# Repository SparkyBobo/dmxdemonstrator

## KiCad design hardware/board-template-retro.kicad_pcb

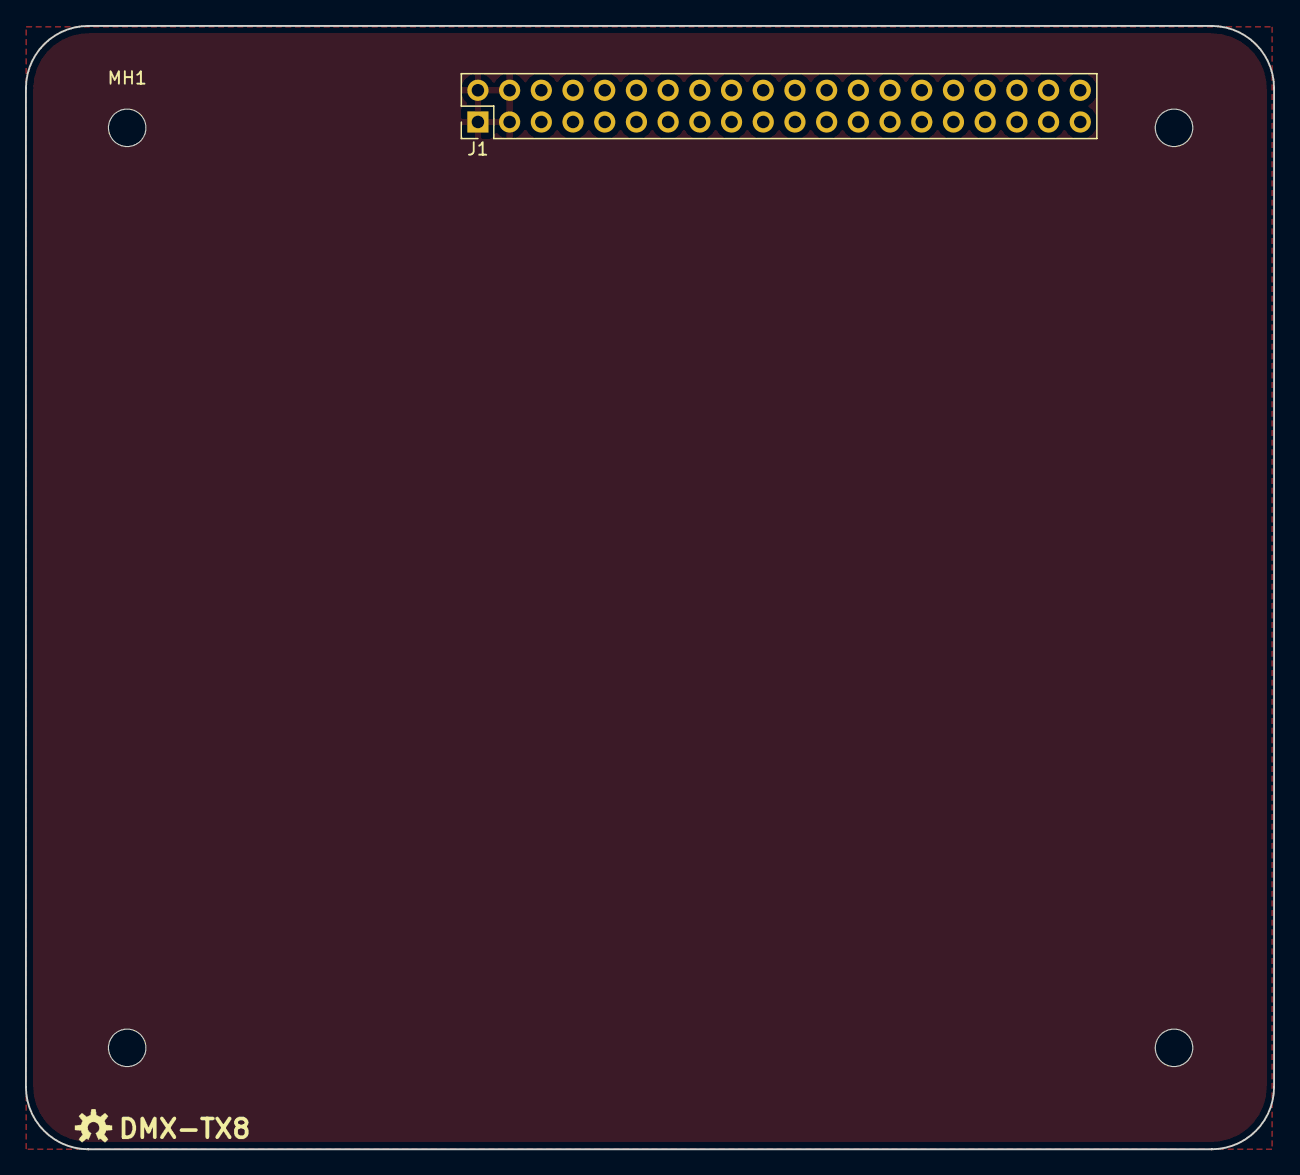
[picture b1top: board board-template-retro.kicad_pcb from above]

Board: 2 copper layers, 100.0 x 90.0 mm, 5 parts (0 on the bottom side), 2 nets, no tracks yet.

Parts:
J1: Expansion; PinHeader_2x20_P2.54mm_Vertical
MH1, MH2, MH3, MH4: MountingHole; MountingHole_3mm

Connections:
+5V: J1.1, J1.2, J1.3, J1.4
GND: J1.37, J1.38, J1.39, J1.40

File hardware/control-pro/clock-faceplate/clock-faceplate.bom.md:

# Bill Of Materials (BOM)

## Schematic

**Filename:** E:\OpenSource\dmxdemonstrator\hardware\control-pro\clock-faceplate\clock-faceplate.sch

**Date Modified:** 4/6/2024 8:51:16 PM

**Kicad Version:** Eeschema (5.1.12)-1

**Component Count:** 17

## Components

Item#|Quantity|Reference|Description|Manufacturer|Part Number|Datasheet|Notes
-----|--------|---------|-----------|------------|-----------|---------|-----
1|1|PCB|Control-Pro Clock Faceplate PCB|OHSPark|DMX-CPCF, Rev 1.3||[Order](https://oshpark.com/shared_projects/S9LARHyr)|
2|4|MH1, MH2, MH3, MH4|Screw, M3 x 8mm||||
<!--BOMROW-->

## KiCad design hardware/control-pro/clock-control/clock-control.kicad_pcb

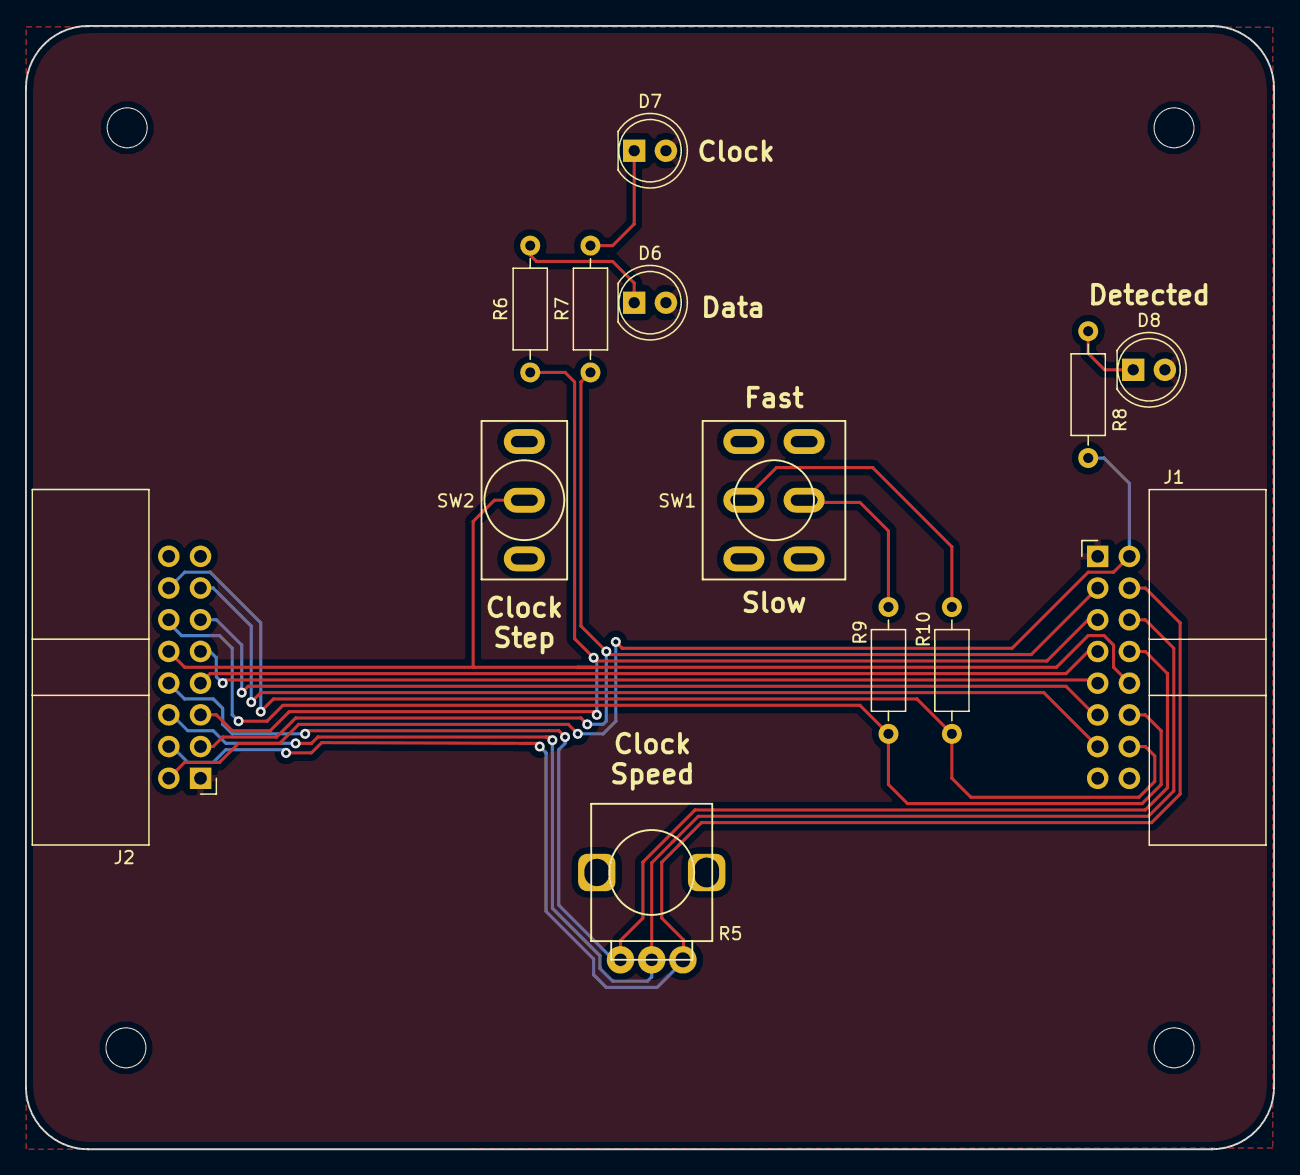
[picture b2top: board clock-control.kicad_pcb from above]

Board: 2 copper layers, 100.0 x 90.0 mm, 17 parts (0 on the bottom side), 20 nets.

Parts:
D6: DATA; LED_D5.0mm
D7: CLOCK; LED_D5.0mm
D8: ACTIVE; LED_D5.0mm
J1: OUTPUT; IDC-Header_2x08_P2.54mm_Horizontal
J2: INPUT; IDC-Header_2x08_P2.54mm_Horizontal
MH1, MH2, MH3, MH4: MountingHole; MountingHole_3.2mm_M3
R5: 10k; BOURNS_PTV09A_1
R6, R7, R8, R9, R10: 330; R_Axial_DIN0207_L6.3mm_D2.5mm_P10.16mm_Horizontal
SW1: CLOCK_SPEED; ESWITCH_100_DPDT_M1
SW2: CLOCK_STEP; ESWITCH_100_SPDT_M1

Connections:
+5V: D6.2, D7.2, D8.2, J1.1, J2.1
/DIM1: J1.7, J2.7
/DIM2: J1.9, J2.9
/DIM3: J1.11, J2.11
/DIM4: J1.13, J2.13
/SPD_HI: J1.4, J2.4, R5.3
/SPD_LO: J1.8, J2.8, R5.1
/SPD_WIPER: J1.6, J2.6, R5.2
/~CLK_FST: J1.14, J2.14, R10.1
/~CLK_SLO: J1.12, J2.12, R9.1
/~CLK_STEP: J1.10, J2.10, SW2.2
/~CLOCK: J1.3, J2.3, R7.1
/~DATA: J1.5, J2.5, R6.1
/~HWD_DT: J1.2, J2.2, R8.1
GND: J1.15, J1.16, J2.15, J2.16, SW1.3, SW1.4, SW2.3
unnamed: D6.1, R6.2
unnamed: D7.1, R7.2
unnamed: D8.1, R8.2
unnamed: R9.2, SW1.2
unnamed: R10.2, SW1.5

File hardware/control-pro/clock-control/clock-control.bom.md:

# Bill Of Materials (BOM)

## Schematic

**Filename:** E:\OpenSource\dmxdemonstrator\hardware\control-pro\clock-control\clock-control.sch

**Date Modified:** 4/8/2024 1:51:22 PM

**Kicad Version:** Eeschema (5.1.12)-1

**Component Count:** 17

## Components

Item#|Quantity|Reference|Description|Manufacturer|Part Number|Datasheet|Notes
-----|--------|---------|-----------|------------|-----------|---------|-----
1|1|PCB|Control-Pro Clock Control PCB|OHSPark|DMX-CPCB, Rev 1.3||[Order](https://oshpark.com/shared_projects/llBuRZd8)|
2|1|D6|Green LED, 5mm||||
3|1|D6|LED Spacer, 17mm|Wurth|705820170|[Data Sheet](https://www.we-online.de/katalog/datasheet/705820xxx_overview.pdf)|
4|1|D7|Red LED, 5mm||||
5|1|D7|LED Spacer, 17mm|Wurth|705820170|[Data Sheet](https://www.we-online.de/katalog/datasheet/705820xxx_overview.pdf)|
6|1|D8|Red LED, 5mm||||
7|1|J1|2x8 shrouded right-angle header|Wurth Elektronik|61201621721|[Data Sheet](https://www.we-online.com/components/products/datasheet/6120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|
8|1|J1|2x8 ribbon cable||||
9|1|J2|2x8 shrouded right-angle header|Wurth Elektronik|61201621721|[Data Sheet](https://www.we-online.com/components/products/datasheet/6120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|
10|4|MH1, MH2, MH3, MH4|Standoff, M3 x 18mm|Keystone|24446||
11|4|MH1, MH2, MH3, MH4|Screw, M3 x 8mm||||
12|1|R5|100k potentiometer, audio|Bourns|PTV09A-4030F-A104|[Data Sheet](https://www.bourns.com/docs/Product-Datasheets/PTV09.pdf)|
13|1|R5|potentiometer knob||||
14|5|R6, R7, R8, R9, R10|330 ohm||||
15|1|SW1|DPDT Toggle, On-Off-On|E-Switch|100DP3T1B1M1QEH|[Data Sheet](https://sten-eswitch-13110800-production.s3.amazonaws.com/sy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|
16|1|SW2|SPDT Toggle, On-On momentary|E-Switch|100SP2T1B1M1QEH|[Data Sheet](https://sten-eswitch-13110800-production.s3.amazonaws.com/sy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|
<!--BOMROW-->

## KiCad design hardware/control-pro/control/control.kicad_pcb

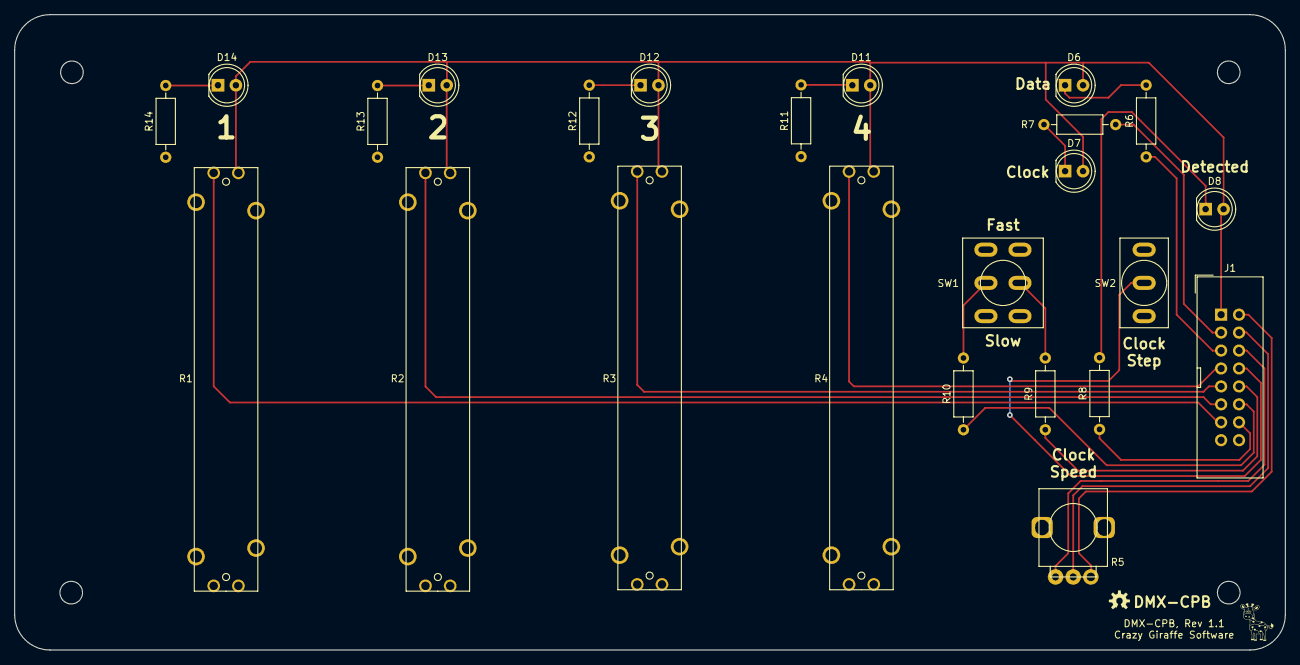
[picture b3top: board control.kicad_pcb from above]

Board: 2 copper layers, 180.0 x 90.0 mm, 28 parts (0 on the bottom side), 24 nets.

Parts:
D6: DATA; LED_D5.0mm
D7: CLOCK; LED_D5.0mm
D8: ACTIVE; LED_D5.0mm
D11: DIM3; LED_D5.0mm
D12: DIM2; LED_D5.0mm
D13: DIM1; LED_D5.0mm
D14: DIM0; LED_D5.0mm
J1: OUTPUT; IDC-Header_2x08_P2.54mm_Vertical
MH1, MH2, MH3, MH4: MountingHole; MountingHole_3.2mm_M3
R1, R2, R3, R4: 10k; BOURNS_PTA4543
R5: 10k; BOURNS_PTV09A_1
R6, R7, R8, R9, R10, R11, R12, R13, R14: 330; R_Axial_DIN0207_L6.3mm_D2.5mm_P10.16mm_Horizontal
SW1: CLOCK_SPEED; ESWITCH_100_DPDT_M1
SW2: CLOCK_STEP; ESWITCH_100_SPDT_M1

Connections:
+5V: D6.2, D7.2, D8.2, D11.2, D12.2, D13.2, D14.2, J1.1, R1.1, R2.1, R3.1, R4.1
GND: J1.15, J1.16, R1.3, R2.3, R3.3, R4.3, R11.1, R12.1, R13.1, R14.1, SW1.3, SW1.4, SW2.3
unnamed: D6.1, R6.2
unnamed: D7.1, R7.2
unnamed: D8.1, R8.2
unnamed: D11.1, R11.2
unnamed: D12.1, R12.2
unnamed: D13.1, R13.2
unnamed: D14.1, R14.2
unnamed: J1.2, R5.3
unnamed: J1.3, R7.1
unnamed: J1.4, R5.2
unnamed: J1.5, R6.1
unnamed: J1.6, R5.1
unnamed: J1.7, R4.2
unnamed: J1.8, SW2.2
unnamed: J1.9, R3.2
unnamed: J1.10, R9.1
unnamed: J1.11, R2.2
unnamed: J1.12, R10.1
unnamed: J1.13, R1.2
unnamed: J1.14, R8.1
unnamed: R9.2, SW1.2
unnamed: R10.2, SW1.5

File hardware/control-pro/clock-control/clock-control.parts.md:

# Parts List

## Schematic

**Filename:** E:\OpenSource\dmxdemonstrator\hardware\control-pro\clock-control\clock-control.sch

**Date Modified:** 4/8/2024 1:51:22 PM

**Kicad Version:** Eeschema (5.1.12)-1

**Component Count:** 17

## Parts


### OHSPark

Reference|Description|Supplier|Part Number|Quantity|Link|Notes
---------|-----------|--------|-----------|--------|----|-----
PCB|Control-Pro Clock Control PCB|OHSPark|DMX-CPCB, Rev 1.3|1|[Order](https://oshpark.com/shared_projects/llBuRZd8)|pack of 3, 2 not used
<!--PARTROW-->

### Sparkfun

Reference|Description|Supplier|Part Number|Quantity|Link|Notes
---------|-----------|--------|-----------|--------|----|-----
D6|Green LED, 5mm|Sparkfun|COM-09592|1|[Order](https://www.sparkfun.com/products/9592)|
D7, D8|Red LED, 5mm|Sparkfun|COM-09590|2|[Order](https://www.sparkfun.com/products/9590)|
R5|potentiometer knob|Sparkfun|COM-11951|1|[Order](https://www.sparkfun.com/products/11951)|goes to 11
R6, R7, R8, R9, R10|330 ohm|Sparkfun|PRT-14490|1|[Order](https://www.sparkfun.com/products/14490)|pack of 20, 15 not used
<!--PARTROW-->

### Adafruit

Reference|Description|Supplier|Part Number|Quantity|Link|Notes
---------|-----------|--------|-----------|--------|----|-----
D6|Green LED, 5mm|Adafruit|298|1|[Order](https://www.adafruit.com/product/298)|pack of 25, 24 not used
D7, D8|Red LED, 5mm|Adafruit|299|1|[Order](https://www.adafruit.com/product/299)|pack of 25, 23 not used
R5|potentiometer knob|Adafruit|5527|1|[Order](https://www.adafruit.com/product/5527)|black, silver, red, blue, gold
R6, R7, R8, R9, R10|330 ohm|Adafruit|2781|1|[Order](https://www.adafruit.com/product/2781)|use 470 ohm instead, pack of 25, 20 not used
<!--PARTROW-->

### Digikey

Reference|Description|Supplier|Part Number|Quantity|Link|Notes
---------|-----------|--------|-----------|--------|----|-----
D6, D7|LED Spacer, 17mm|Digikey|732-11617-ND|2|[Order](https://www.digikey.com/product-detail/en/w%C3%BCrth-elektro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|
J1, J2|2x8 shrouded right-angle header|Digikey| 732-2099-ND|2|[Order](https://www.digikey.com/en/products/detail/w%C3%BCrth-elektr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|
MH1, MH2, MH3, MH4|Standoff, M3 x 18mm|Digikey|36-24446-ND|4|[Order](https://www.digikey.com/product-detail/en/keystone-electroni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|
R5|100k potentiometer, audio|Digikey|PTV09A-4030F-A104-ND|1|[Order](https://www.digikey.com/en/products/detail/bourns-inc/PTV09A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|knob needed
SW1|DPDT Toggle, On-Off-On|Digikey|EG2413-ND|1|[Order](https://www.digikey.com/products/en?keywords=100DP3T1B1M1QEH)|
SW2|SPDT Toggle, On-On momentary|Digikey|EG2373-ND|1|[Order](https://www.digikey.com/product-detail/en/e-switch/100SP2T1B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|
<!--PARTROW-->

### Mouser

Reference|Description|Supplier|Part Number|Quantity|Link|Notes
---------|-----------|--------|-----------|--------|----|-----
D6, D7|LED Spacer, 17mm|Mouser|710-705820170|2|[Order](https://www.mouser.com/ProductDetail/Wurth-Elektronik/705820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|
J1, J2|2x8 shrouded right-angle header|Mouser|710-61201621721|2|[Order](https://www.mouser.com/ProductDetail/Wurth-Elektronik/612016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|
MH1, MH2, MH3, MH4|Standoff, M3 x 18mm|Mouser|534-24436|4|[Order](https://www.mouser.com/ProductDetail/Keystone-Electronics/24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|
R5|100k potentiometer, audio|Mouser|652-PTV09A4030FA104|1|[Order](https://www.mouser.com/ProductDetail/Bourns/PTV09A-4030F-A10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|knob needed
SW1|DPDT Toggle, On-Off-On|Mouser|612-100-H1111|1|[Order](https://www.mouser.com/ProductDetail/E-Switch/100DP3T1B1M1QE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|
SW2|SPDT Toggle, On-On momentary|Mouser|612-100-B1111|1|[Order](https://www.mouser.com/ProductDetail/E-Switch/100SP2T1B1M1QE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|
<!--PARTROW-->

### Newark

Reference|Description|Supplier|Part Number|Quantity|Link|Notes
---------|-----------|--------|-----------|--------|----|-----
J1, J2|2x8 shrouded right-angle header|Newark|19P1272|2|[Order](https://www.newark.com/wurth-elektronik/61201621721/wire-to-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|
<!--PARTROW-->

### Amazon

Reference|Description|Supplier|Part Number|Quantity|Link|Notes
---------|-----------|--------|-----------|--------|----|-----
J1|2x8 ribbon cable|Amazon||1|[Order](https://www.amazon.com/s?k=16-Pin+IDC+Connector+Flat+Ribbon+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|
MH1, MH2, MH3, MH4|Standoff, M3 x 18mm|Amazon||4|[Order](https://www.amazon.com/s?k=m3+18mm+standoff)|
MH1, MH2, MH3, MH4|Screw, M3 x 8mm|Amazon||4|[Order](https://www.amazon.com/s?k=m3+8mm+screw)|
<!--PARTROW-->

### Ebay

Reference|Description|Supplier|Part Number|Quantity|Link|Notes
---------|-----------|--------|-----------|--------|----|-----
MH1, MH2, MH3, MH4|Standoff, M3 x 18mm|Ebay||1|[Order](https://www.ebay.com/itm/M3-Aluminum-Alloy-Female-Hex-Hexago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|pack of 10, 6 not used
<!--PARTROW-->
<!--VENDORLIST-->

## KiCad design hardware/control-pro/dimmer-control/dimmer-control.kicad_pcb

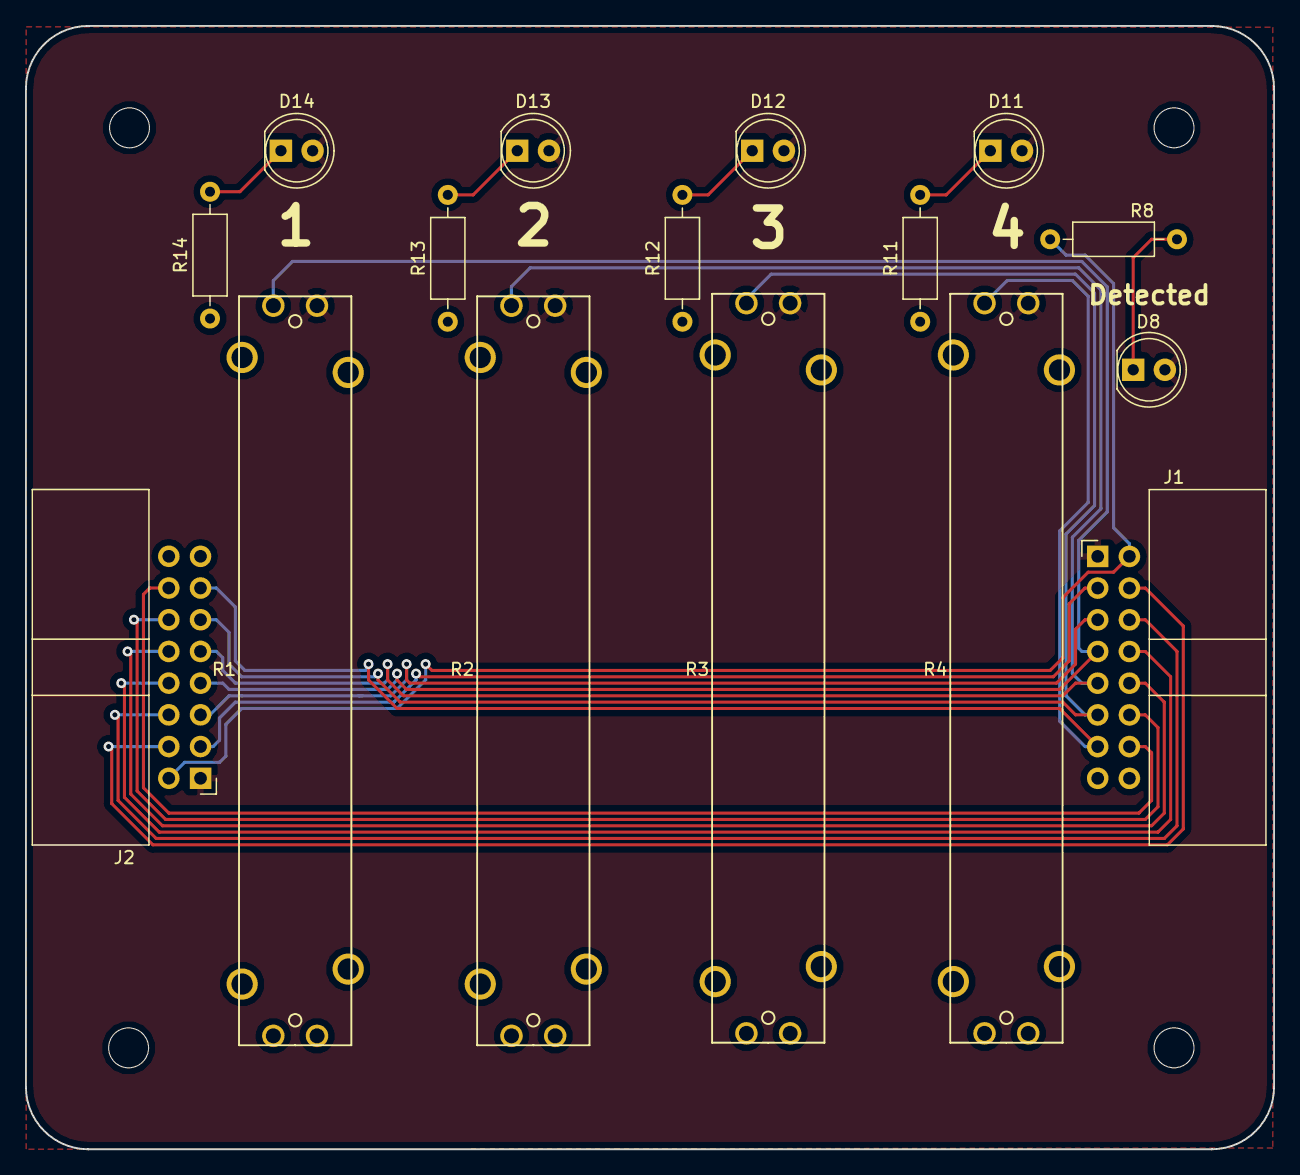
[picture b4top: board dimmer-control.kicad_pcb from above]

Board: 2 copper layers, 100.0 x 90.0 mm, 20 parts (0 on the bottom side), 20 nets.

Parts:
D8: LED; LED_D5.0mm
D11: DIM4; LED_D5.0mm
D12: DIM3; LED_D5.0mm
D13: DIM2; LED_D5.0mm
D14: DIM1; LED_D5.0mm
J1: OUTPUT; IDC-Header_2x08_P2.54mm_Horizontal
J2: INPUT; IDC-Header_2x08_P2.54mm_Horizontal
MH1, MH2, MH3, MH4: MountingHole; MountingHole_3.2mm_M3
R1, R2, R3, R4: 10k; BOURNS_PTA4543
R8, R11, R12, R13, R14: 330; R_Axial_DIN0207_L6.3mm_D2.5mm_P10.16mm_Horizontal

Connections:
+5V: D8.2, D11.2, D12.2, D13.2, D14.2, J1.1, J2.1, R1.1, R2.1, R3.1, R4.1
/DIM1: J1.7, J2.7, R1.2
/DIM2: J1.9, J2.9, R2.2
/DIM3: J1.11, J2.11, R3.2
/DIM4: J1.13, J2.13, R4.2
/SPD_HI: J1.4, J2.4
/SPD_LO: J1.8, J2.8
/SPD_WIPER: J1.6, J2.6
/~CLK_FST: J1.14, J2.14
/~CLK_SLO: J1.12, J2.12
/~CLK_STEP: J1.10, J2.10
/~CLOCK: J1.3, J2.3
/~DATA: J1.5, J2.5
/~HWD_DT: J1.2, J2.2, R8.1
GND: J1.15, J1.16, J2.15, J2.16, R1.3, R2.3, R3.3, R4.3, R11.1, R12.1, R13.1, R14.1
unnamed: D8.1, R8.2
unnamed: D11.1, R11.2
unnamed: D12.1, R12.2
unnamed: D13.1, R13.2
unnamed: D14.1, R14.2

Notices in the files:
hardware/board-template-retro.kicad_pcb:
https://creativecommons.org/licenses/by-sa/4.0
Released under the Creative Commons Attribution Share-Alike 4.0 License
hardware/control-pro/clock-control/clock-control.kicad_pcb:
Released under the Creative Commons Attribution Share-Alike 4.0m License
